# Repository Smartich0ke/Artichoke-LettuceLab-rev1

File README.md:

# Artichoke LettuceLab rev1

For more information please see my website at: https://hackaday.io/project/170160-artichoke-lettucelab-rev-10#header

Please feel free to join this repository if you are interested or email me at: pitsnthings@gmail.com

The Artichoke LettuceLab Arduino Mega sheild is designed to make the construction of small arduino robots much easier and less time consuming. It can drive 2 motors (or one stepper motor), a I2C interfaced LCD display, an ultrasonic distance sensor, an LDR sensor, 2 headlights, 2 blinkers, 2 tail lights, 5 LEDS, 6 buttons and it even includes a MCP23017 GPIO expander to give you another 16 I/O pins.

FILES:

lettucelab-master.zip : All nececarry gerber files compressed into a zip file.

pcb-files : all kicad pcb files, inside that is "gerbers1.0"  which has all the gerbers in it.

wheels1.0.ino : Example Arduino sketch for wheels and lights.

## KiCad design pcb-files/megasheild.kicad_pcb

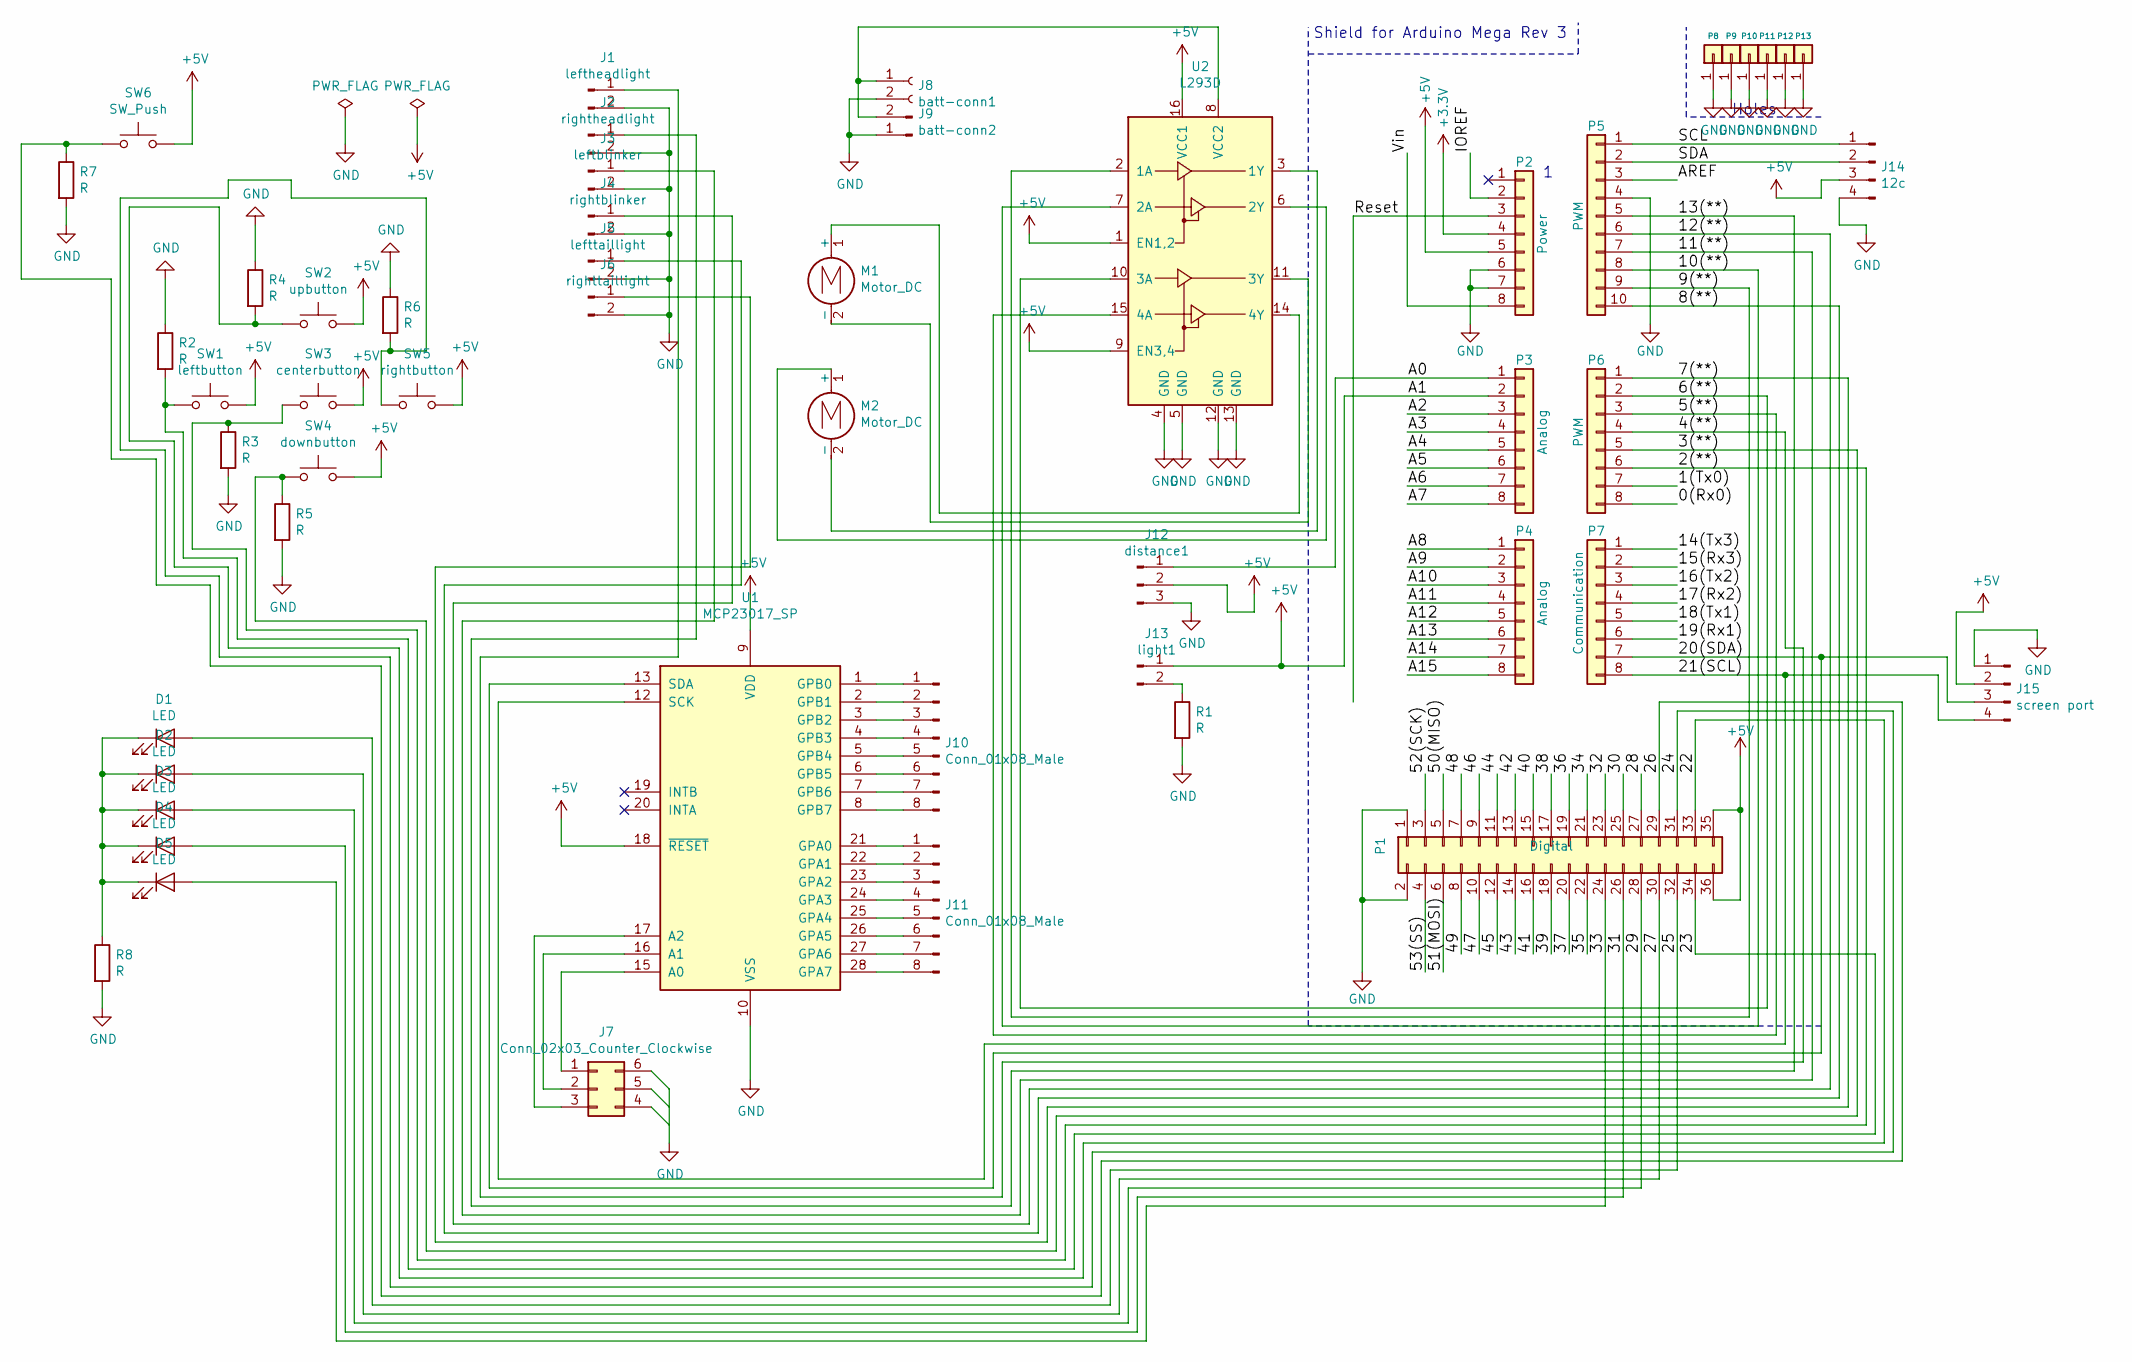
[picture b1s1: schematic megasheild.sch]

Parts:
D1, D2, D3, D4, D5: LED; LED_D3.0mm
J1: leftheadlight; PinHeader_1x02_P2.54mm_Vertical
J2: rightheadlight; PinHeader_1x02_P2.54mm_Vertical
J3: leftblinker; PinHeader_1x02_P2.54mm_Vertical
J4: rightblinker; PinHeader_1x02_P2.54mm_Vertical
J5: lefttaillight; PinHeader_1x02_P2.54mm_Vertical
J6: righttaillight; PinHeader_1x02_P2.54mm_Vertical
J7: Conn_02x03_Counter_Clockwise; PinHeader_2x03_P2.54mm_Vertical
J8: batt-conn1; PinHeader_1x02_P2.54mm_Vertical
J9: batt-conn2; PinSocket_1x02_P2.54mm_Vertical
J10, J11: Conn_01x08_Male; PinHeader_1x08_P2.54mm_Vertical
J12: distance1; PinHeader_1x03_P2.54mm_Vertical
J13: light1; PinHeader_1x02_P2.54mm_Vertical
J14: 12c; PinHeader_1x04_P2.54mm_Vertical
J15: screen port; PinHeader_1x04_P2.54mm_Vertical
M1, M2: Motor_DC; PinHeader_1x02_P2.54mm_Vertical
P1: Digital; Socket_Strip_Arduino_2x18
P2: Power; Socket_Strip_Arduino_1x08
P3, P4: Analog; Socket_Strip_Arduino_1x08
P5: PWM; Socket_Strip_Arduino_1x10
P6: PWM; Socket_Strip_Arduino_1x08
P7: Communication; Socket_Strip_Arduino_1x08
P8, P9, P10, P11, P12, P13: CONN_01X01; Arduino_1pin
R1, R2, R3, R4, R5, R6, R7, R8: R; R_Axial_DIN0204_L3.6mm_D1.6mm_P2.54mm_Vertical
SW1: leftbutton; SW_PUSH_6mm
SW2: upbutton; SW_PUSH_6mm
SW3: centerbutton; SW_PUSH_6mm
SW4: downbutton; SW_PUSH_6mm
SW5: rightbutton; SW_PUSH_6mm
SW6: SW_Push; SW_PUSH_6mm
U1: MCP23017_SP; DIP-28_W7.62mm
U2: L293D; DIP-16_W7.62mm

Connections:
+3V3: P2.4
+5V: J12.2, J13.1, J14.3, J15.2, P1.35, P1.36, P2.5, P3.2, SW1.2, SW2.2, SW3.2, SW4.2, SW5.2, SW6.2, U1.9 (VDD), U1.18 (~RESET~), U2.1 (EN1,2), U2.9 (EN3,4), U2.16 (VCC1)
/0(Rx0): P6.8
/1(Tx0): P6.7
/2(**): P6.6, R3.1, SW3.1
/3(**): P6.5, R5.1, SW4.1
/4(**): J1.1, P6.4
/5(**): P6.3, U2.15 (4A)
/6(**): P6.2, U2.10 (3A)
/7(**): J6.1, P6.1
/8(**): J5.1, P5.10
/9(**): P5.9, U2.2 (1A)
/10(**): P5.8, U2.7 (2A)
/11(**): J3.1, P5.7
/12(**): J4.1, P5.6
/13(**): J2.1, P5.5
/14(Tx3): P7.1
/15(Rx3): P7.2
/16(Tx2): P7.3
/17(Rx2): P7.4
/18(Tx1): P7.5
/19(Rx1): P7.6
/20(SDA): J15.3, P7.7, U1.13 (SDA)
/21(SCL): J15.4, P7.8, U1.12 (SCK)
/22: P1.33, R4.2, SW2.1
/23: P1.34, R2.2, SW1.1
/24: P1.31, R6.2, SW5.1
/25: D1.2 (A), P1.32
/26: P1.29, R7.1, SW6.1
/27: D2.2 (A), P1.30
/28: P1.27
/29: D3.2 (A), P1.28
/30: P1.25
/31: D4.2 (A), P1.26
/32: P1.23
/33: D5.2 (A), P1.24
/34: P1.21
/35: P1.22
/36: P1.19
/37: P1.20
/38: P1.17
/39: P1.18
/40: P1.15
/41: P1.16
/42: P1.13
/43: P1.14
/44: P1.11
/45: P1.12
/46: P1.9
/47: P1.10
/48: P1.7
/49: P1.8
/50(MISO): P1.5
/51(MOSI): P1.6
/52(SCK): P1.3
/53(SS): P1.4
/A0: J12.1, P3.1
/A2: P3.3
/A3: P3.4
/A4: P3.5
/A5: P3.6
/A6: P3.7
/A7: P3.8
/A8: P4.1
/A9: P4.2
/A10: P4.3
/A11: P4.4
/A12: P4.5
/A13: P4.6
/A14: P4.7
/A15: P4.8
/AREF: P5.3
/IOREF: P2.2
/Reset: P2.3
/SCL: J14.1, P5.1
/SDA: J14.2, P5.2
/Vin: P2.8
GND: J1.2, J2.2, J3.2, J4.2, J5.2, J6.2, J8.2, J9.1, J12.3, J14.4, J15.1, P1.1, P1.2, P2.6, P2.7, P5.4, P8.1, P9.1, P10.1, P11.1, P12.1, P13.1, R1.2, R2.1, R3.2, R4.1, R5.2, R6.1, R7.2, R8.2, U1.10 (VSS), U2.4 (GND), U2.5 (GND), U2.12 (GND), U2.13 (GND)
unnamed: D1.1 (K), D2.1 (K), D3.1 (K), D4.1 (K), D5.1 (K), R8.1
unnamed: J7.1, U1.15 (A0)
unnamed: J7.2, U1.16 (A1)
unnamed: J7.3, U1.17 (A2)
unnamed: J8.1, J9.2, U2.8 (VCC2)
unnamed: J10.1, U1.1 (GPB0)
unnamed: J10.2, U1.2 (GPB1)
unnamed: J10.3, U1.3 (GPB2)
unnamed: J10.4, U1.4 (GPB3)
unnamed: J10.5, U1.5 (GPB4)
unnamed: J10.6, U1.6 (GPB5)
unnamed: J10.7, U1.7 (GPB6)
unnamed: J10.8, U1.8 (GPB7)
unnamed: J11.1, U1.21 (GPA0)
unnamed: J11.2, U1.22 (GPA1)
unnamed: J11.3, U1.23 (GPA2)
unnamed: J11.4, U1.24 (GPA3)
unnamed: J11.5, U1.25 (GPA4)
unnamed: J11.6, U1.26 (GPA5)
unnamed: J11.7, U1.27 (GPA6)
unnamed: J11.8, U1.28 (GPA7)
unnamed: J13.2, R1.1
unnamed: M1.1 (+), U2.14 (4Y)
unnamed: M1.2 (-), U2.11 (3Y)
unnamed: M2.1 (+), U2.6 (2Y)
unnamed: M2.2 (-), U2.3 (1Y)

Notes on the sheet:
Shield for Arduino Mega Rev 3
Holes

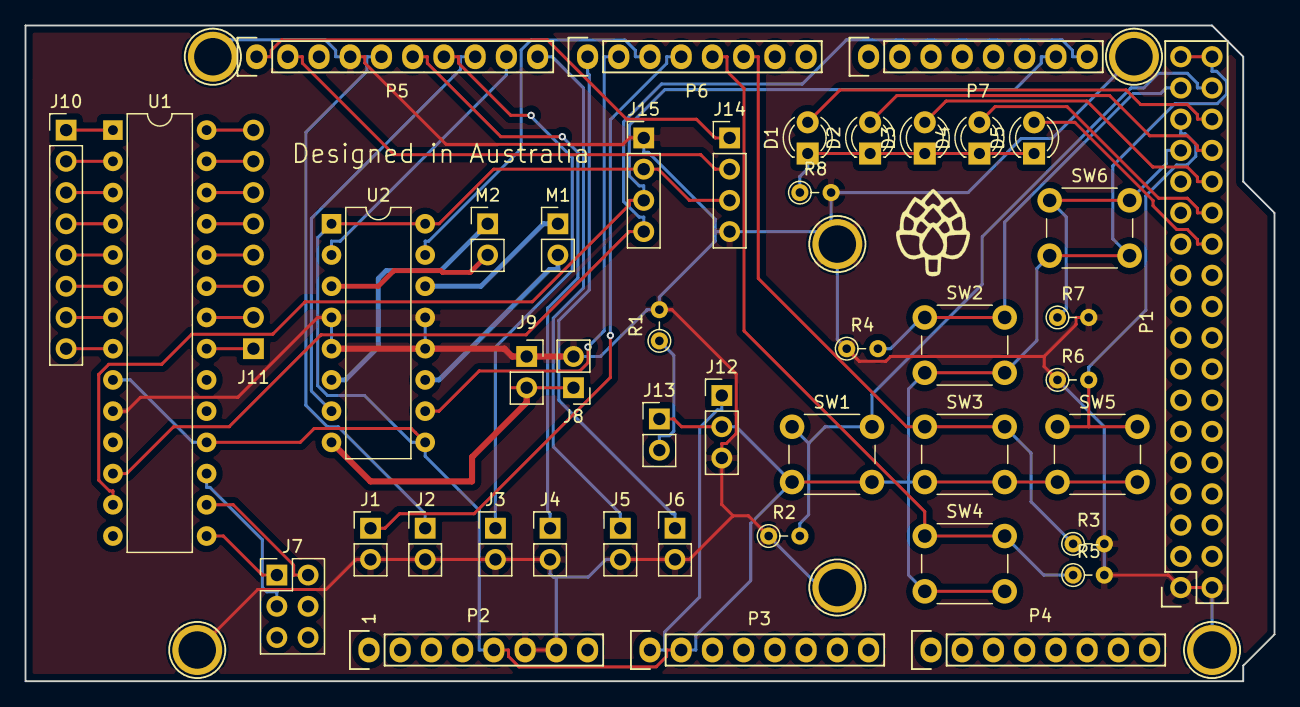
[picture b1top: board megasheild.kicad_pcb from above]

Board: 2 copper layers, 101.6 x 53.3 mm, 51 parts (1 on the bottom side), 54 nets.

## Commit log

2020-03-01 Update readme
    just put some content in it.
2020-03-01 added gerbers
2020-03-01 updated file
2020-03-01 all pcb files
2020-03-01 added more file descriptions
2020-03-01 added arduino sketch
2020-03-01 added file description
2020-04-04 added schematic
